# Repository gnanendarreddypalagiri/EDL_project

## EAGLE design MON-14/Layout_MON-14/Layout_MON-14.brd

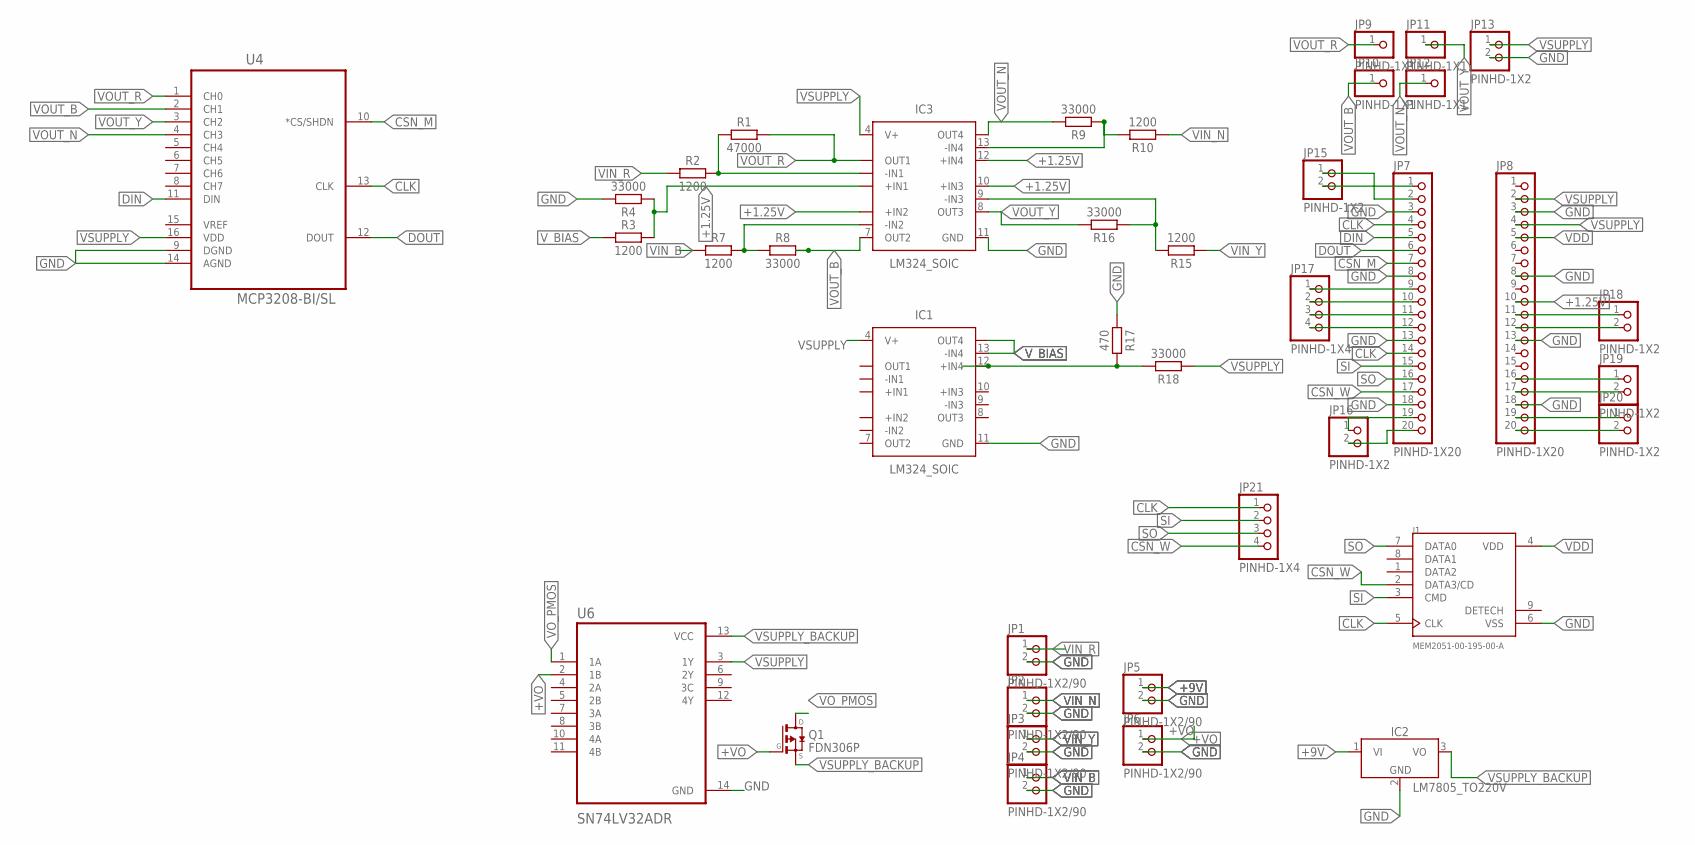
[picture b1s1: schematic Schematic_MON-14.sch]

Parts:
IC1, IC3: LM324_SOIC; SOIC127P600X175-14N
IC2: LM7805_TO220V; TO220V
J1: MEM2051-00-195-00-A; GCT_MEM2051-00-195-00-A
JP1, JP2, JP3, JP4, JP5, JP6: PINHD-1X2/90; 1X02/90
JP7, JP8: PINHD-1X20; 1X20
JP9, JP10, JP11, JP12: PINHD-1X1; 1X01
JP13, JP15, JP16, JP18, JP19, JP20: PINHD-1X2; 1X02
JP17, JP21: PINHD-1X4; 1X04
Q1: FDN306P; SSOT-3
R1: 47000; RESC3216X70
R2, R3, R7, R10, R15: 1200; RESC3216X70
R4, R8, R9, R16, R18: 33000; RESC3216X70
R17: 470; RESC3216X70
U4: MCP3208-BI/SL; SOIC127P600X175-16N
U6: SN74LV32ADR; SOIC127P600X175-14N

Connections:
+1.25V: IC3.3 (+IN1), IC3.5 (+IN2), IC3.10 (+IN3), IC3.12 (+IN4), JP8.10, R3.2, R4.1
+9V: IC2.1 (VI), JP5.1
+VO: JP6.1, Q1.1 (G), U6.2 (1B)
CLK: J1.5 (CLK), JP7.4, JP7.14, JP21.1, U4.13 (CLK)
CSN_M: JP7.7, U4.10 (*CS/SHDN)
CSN_W: J1.2 (DATA3/CD), JP7.17, JP21.4
DIN: JP7.5, U4.11 (DIN)
DOUT: JP7.6, U4.12 (DOUT)
GND: IC1.11 (GND), IC2.2 (GND), IC3.11 (GND), J1.6 (VSS), JP1.2, JP2.2, JP3.2, JP4.2, JP5.2, JP6.2, JP7.3, JP7.8, JP7.13, JP7.18, JP8.3, JP8.8, JP8.13, JP8.18, JP13.2, R4.2, R17.1, U4.9 (DGND), U4.14 (AGND), U6.14 (GND)
unnamed: JP8.20, JP20.2
unnamed: JP8.19, JP20.1
unnamed: JP8.17, JP19.2
unnamed: IC3.6 (-IN2), R7.2, R8.1
unnamed: IC3.9 (-IN3), R15.2, R16.1
unnamed: JP8.16, JP19.1
unnamed: JP7.9, JP17.1
unnamed: IC3.2 (-IN1), R1.1, R2.2
unnamed: IC3.13 (-IN4), R9.1, R10.2
unnamed: JP7.10, JP17.2
unnamed: JP7.11, JP17.3
unnamed: JP7.12, JP17.4
unnamed: IC1.12 (+IN4), R17.2, R18.2
unnamed: JP7.19, JP16.1
unnamed: JP7.20, JP16.2
unnamed: JP7.1, JP15.2
unnamed: JP7.2, JP15.1
unnamed: JP8.11, JP18.1
unnamed: JP8.12, JP18.2
SI: J1.3 (CMD), JP7.15, JP21.2
SO: J1.7 (DATA0), JP7.16, JP21.3
VDD: J1.4 (VDD), JP8.5
VIN_B: JP4.1, R7.1
VIN_N: JP2.1, R10.1
VIN_R: JP1.1, R2.1
VIN_Y: JP3.1, R15.1
VOUT_B: IC3.7 (OUT2), JP10.1, R8.2, U4.2 (CH1)
VOUT_N: IC3.14 (OUT4), JP12.1, R9.2, U4.4 (CH3)
VOUT_R: IC3.1 (OUT1), JP9.1, R1.2, U4.1 (CH0)
VOUT_Y: IC3.8 (OUT3), JP11.1, R16.2, U4.3 (CH2)
VO_PMOS: Q1.3 (D), U6.1 (1A)
VSUPPLY: IC1.4 (V+), IC3.4 (V+), JP8.2, JP8.4, JP13.1, R18.1, U4.16 (VDD), U6.3 (1Y)
VSUPPLY_BACKUP: IC2.3 (VO), Q1.2 (S), U6.13 (VCC)
V_BIAS: IC1.13 (-IN4), IC1.14 (OUT4), R3.1

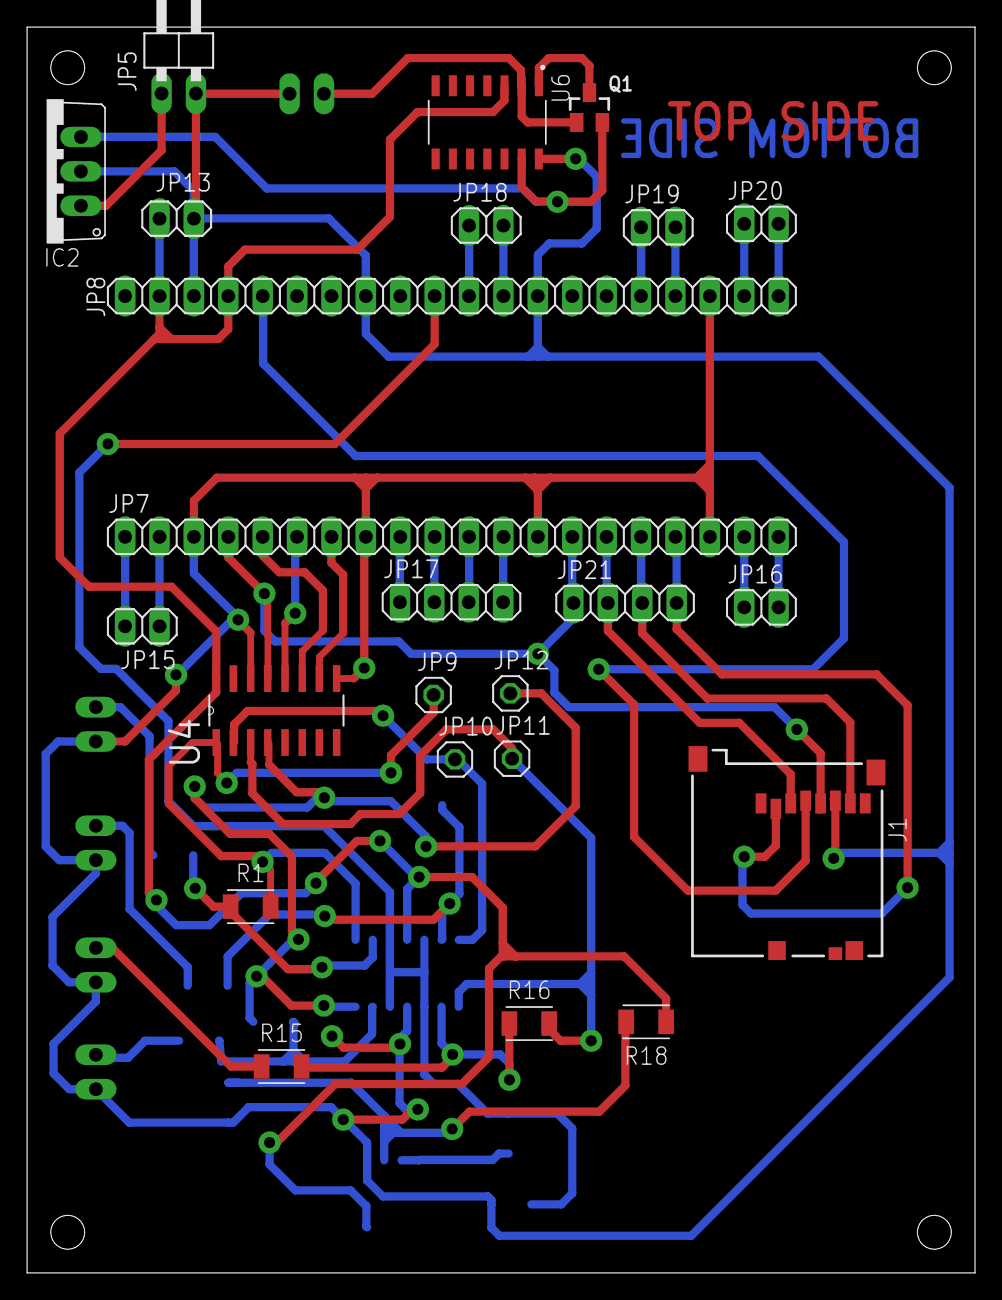
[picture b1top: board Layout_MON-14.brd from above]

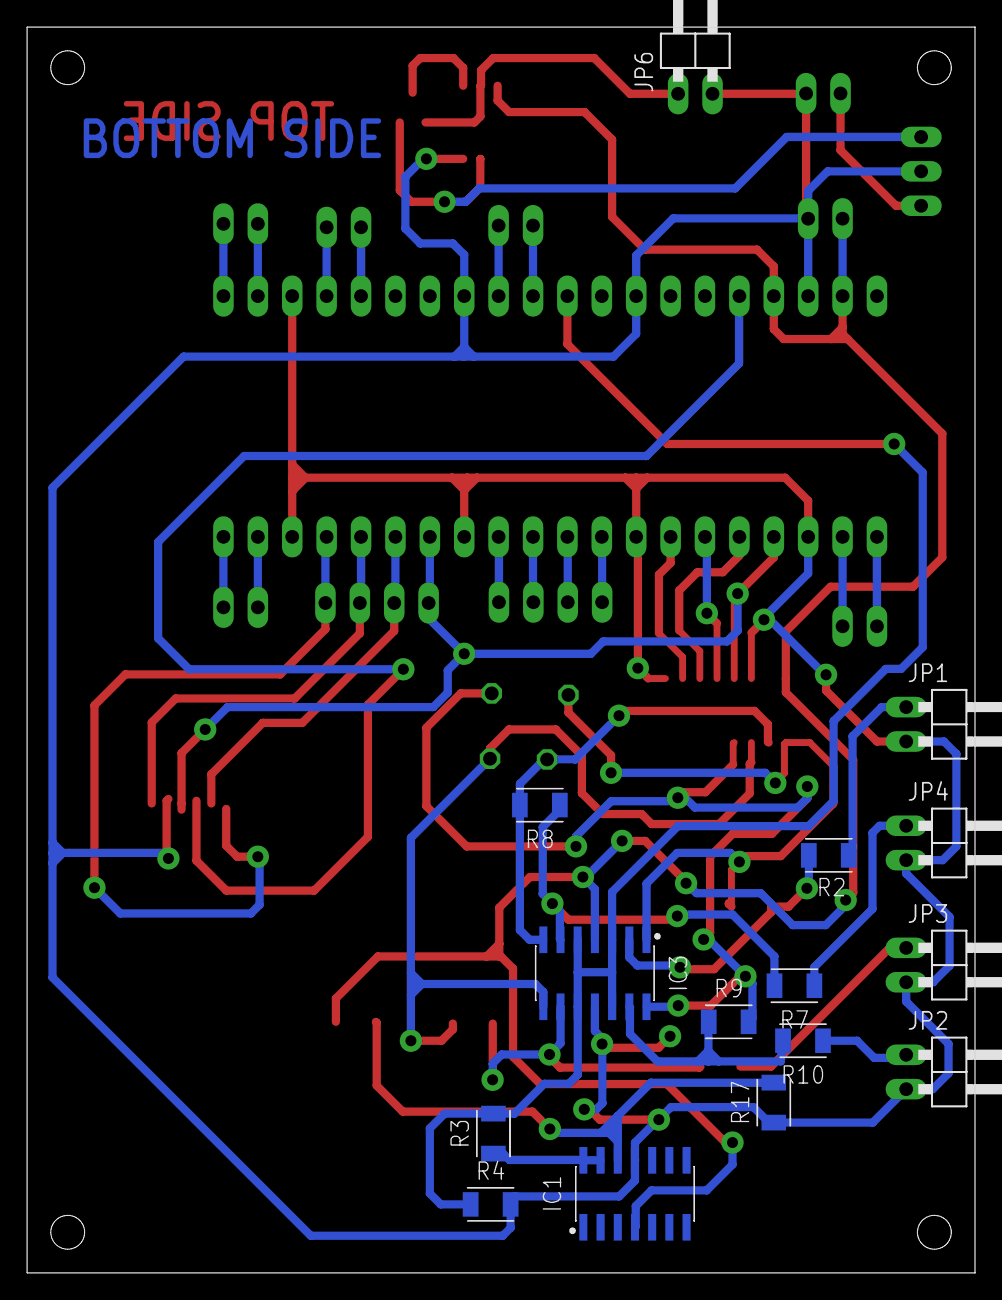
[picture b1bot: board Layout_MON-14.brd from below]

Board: 2 copper layers, 70.0 x 92.0 mm, 39 parts (15 on the bottom side), 43 nets.

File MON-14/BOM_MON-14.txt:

Partlist exported from C:/Users/bhuva/AppData/Local/Temp/Neutron/ElectronFileOutput/18356/sch-97a4a485-1753-4ff7-8d1d-11e111b115d7/Schematic_v52_23 v1.sch at 26-04-2023 19:22

Qty Value               Device                   Package                 Parts                              Description                                                    
5   1200                R_CHIP-1206(3216-METRIC) RESC3216X70             R2, R3, R7, R10, R15               Resistor Fixed - Generic                                       
5   33000               R_CHIP-1206(3216-METRIC) RESC3216X70             R4, R8, R9, R16, R18               Resistor Fixed - Generic                                       
1   470                 R_CHIP-1206(3216-METRIC) RESC3216X70             R17                                Resistor Fixed - Generic                                       
1   47000               R_CHIP-1206(3216-METRIC) RESC3216X70             R1                                 Resistor Fixed - Generic                                       
1   FDN306P             FDN306P                  SSOT-3                  Q1                                 P-Channel MOSFET                                               
2   LM324_SOIC          LM324_SOIC               SOIC127P600X175-14N     IC1, IC3                           Quad-Operational Amplifiers                                    
1   LM7805_TO220V       LM7805_TO220V            TO220V                  IC2                                5V Voltage Regulator                                           
1   MCP3208-BI/SL       MCP3208-BI/SL            SOIC127P600X175-16N     U4                                 IC, 12 ADC, SMD, 3208                                          
1   MEM2051-00-195-00-A MEM2051-00-195-00-A      GCT_MEM2051-00-195-00-A J1                                 Connector, Memory Card,Micro Sd, 8 Position, 1.1mm,FullReel 
4   PINHD-1X1           PINHD-1X1                1X01                    JP9, JP10, JP11, JP12              PIN HEADER                                                     
6   PINHD-1X2           PINHD-1X2                1X02                    JP13, JP15, JP16, JP18, JP19, JP20 PIN HEADER                                                     
6   PINHD-1X2/90        PINHD-1X2/90             1X02/90                 JP1, JP2, JP3, JP4, JP5, JP6       PIN HEADER                                                     
2   PINHD-1X20          PINHD-1X20               1X20                    JP7, JP8                           PIN HEADER                                                     
2   PINHD-1X4           PINHD-1X4                1X04                    JP17, JP21                         PIN HEADER                                                     
1   SN74LV32ADR         SN74LV32ADR              SOIC127P600X175-14N     U6                                 None
